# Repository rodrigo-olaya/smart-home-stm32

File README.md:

# smart-home-stm32
Smart Home on STM32F4 board.

## Build and flash
```
make clean && make
openocd -f board/stm32f4discovery.cfg -c "program firmware.elf verify reset exit"
```

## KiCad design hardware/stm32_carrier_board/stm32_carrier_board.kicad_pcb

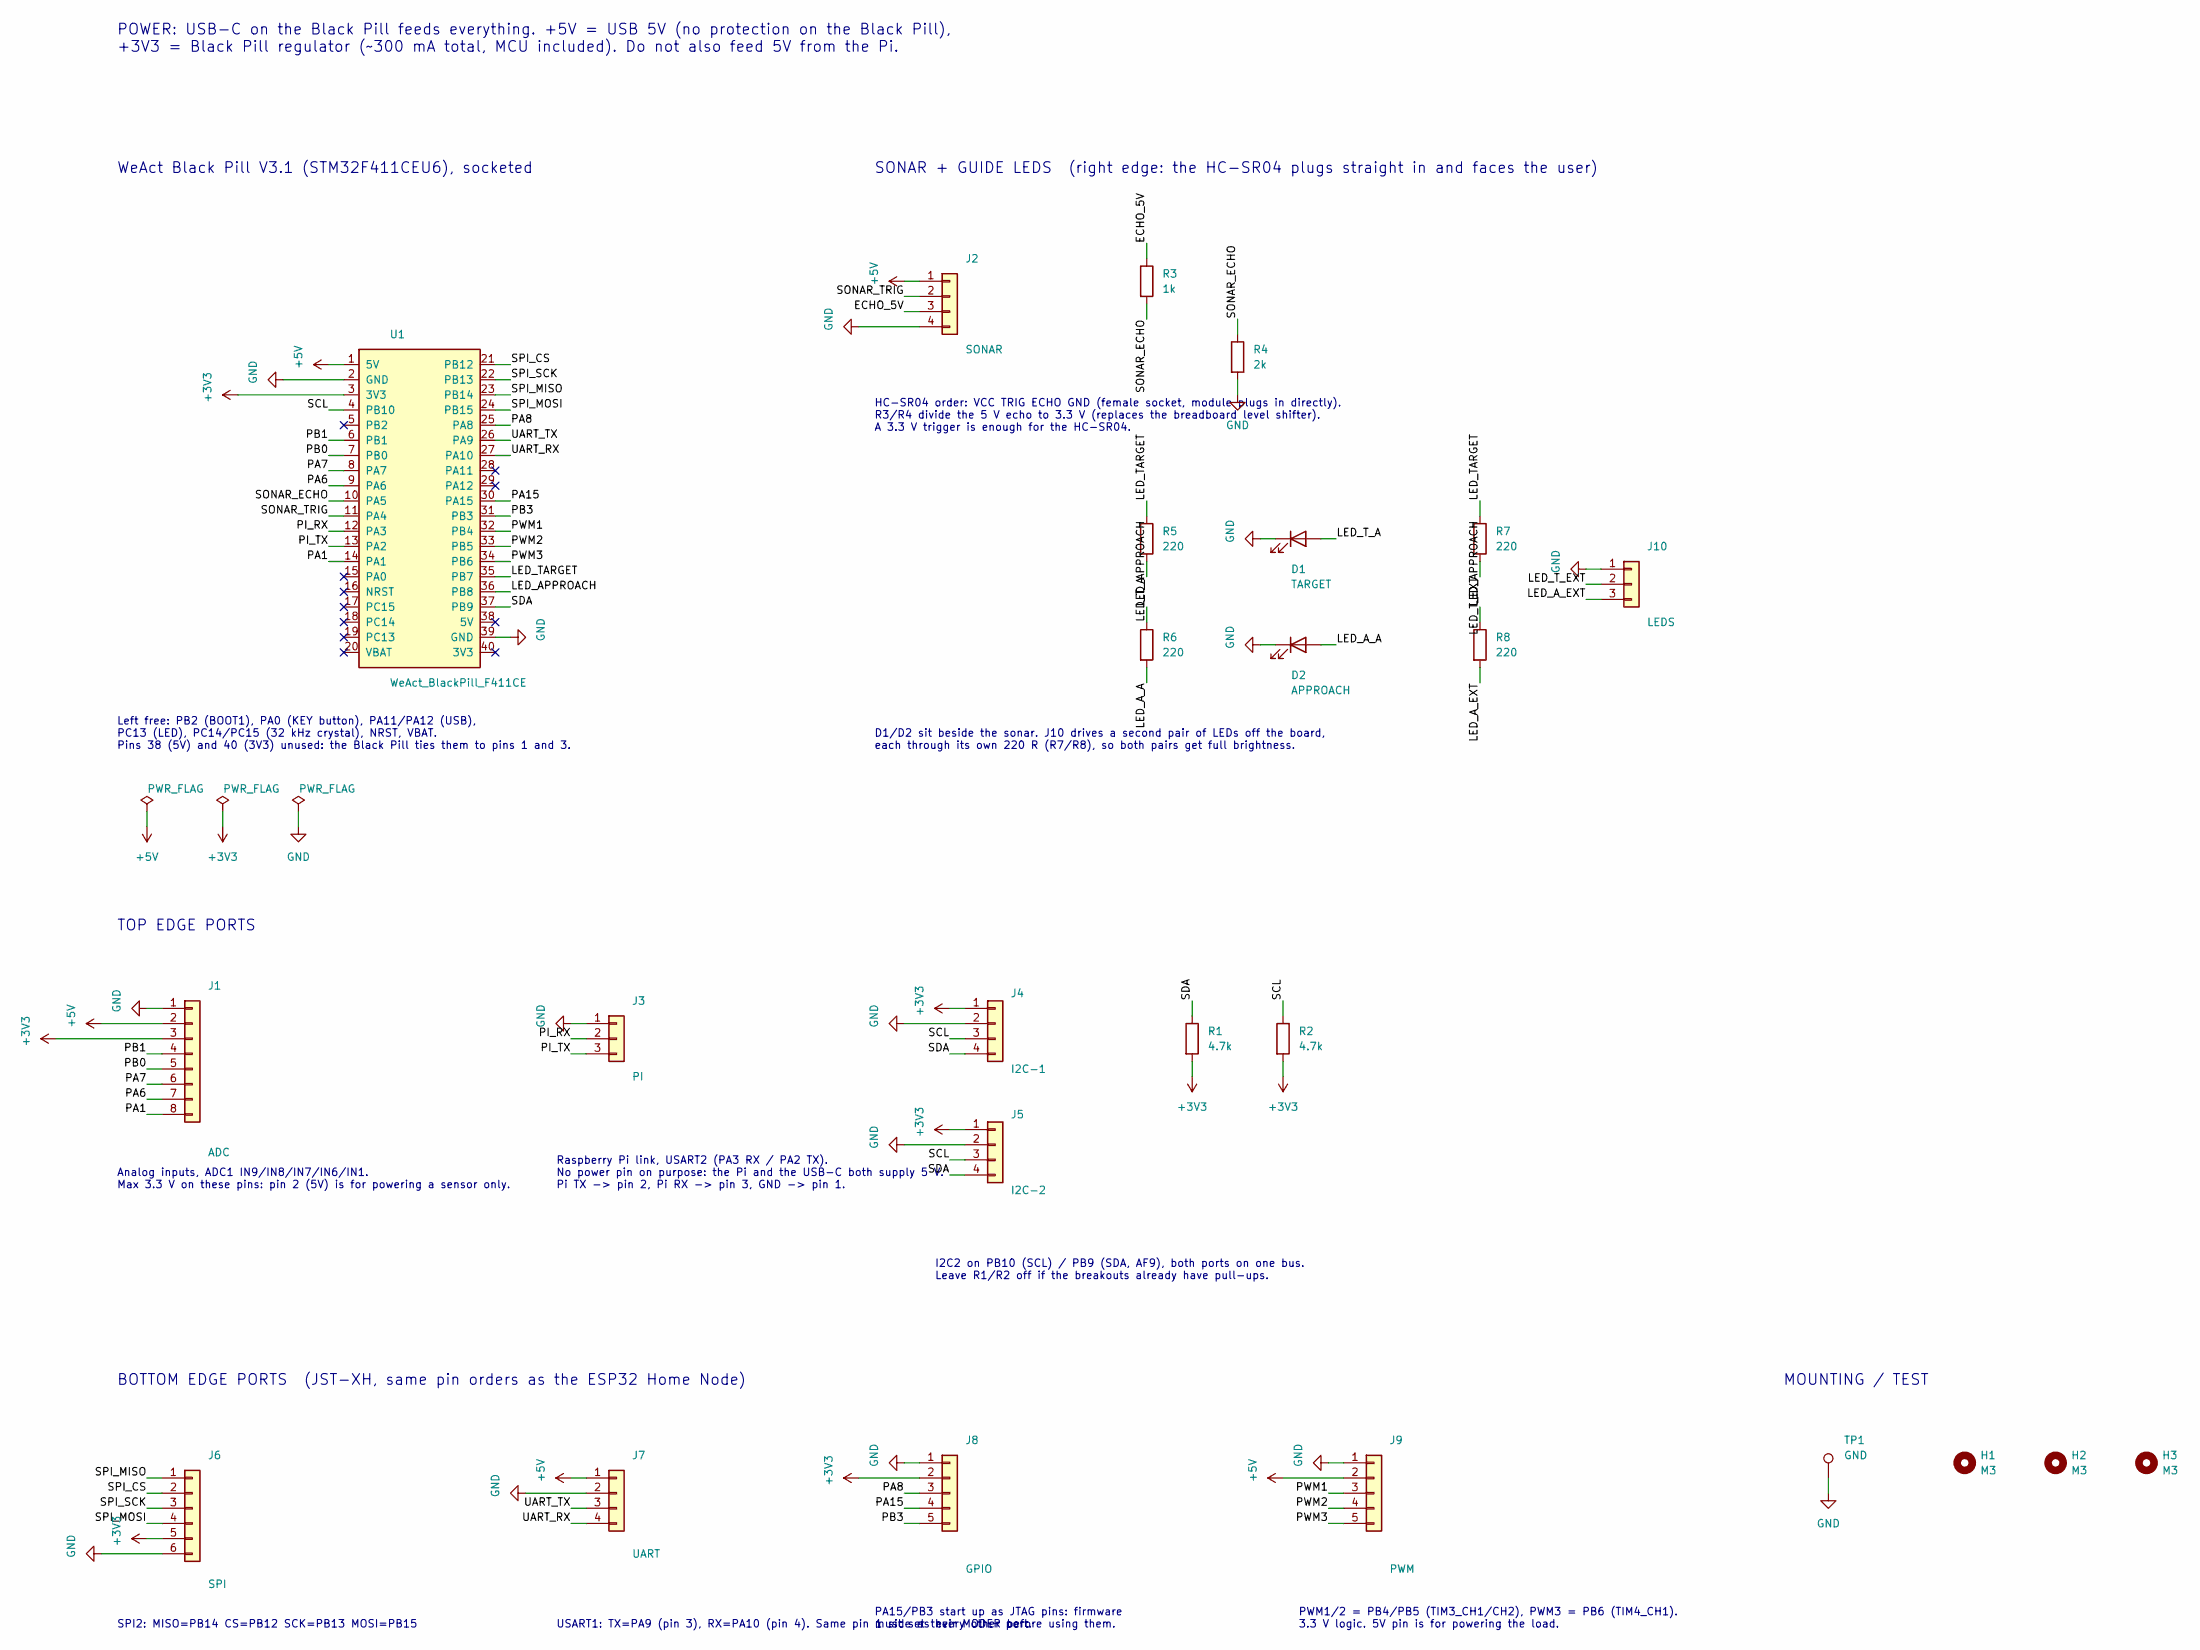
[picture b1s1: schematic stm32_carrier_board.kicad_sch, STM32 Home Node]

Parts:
D1: TARGET; LED_D5.0mm
D2: APPROACH; LED_D5.0mm
H1, H2, H3: M3; MountingHole_3.2mm_M3
J1: ADC; JST_XH_B8B-XH-A_1x08_P2.50mm_Vertical
J2: SONAR; PinSocket_1x04_P2.54mm_Vertical
J3: PI; JST_XH_B3B-XH-A_1x03_P2.50mm_Vertical
J4: I2C-1; JST_XH_B4B-XH-A_1x04_P2.50mm_Vertical
J5: I2C-2; JST_XH_B4B-XH-A_1x04_P2.50mm_Vertical
J6: SPI; JST_XH_B6B-XH-A_1x06_P2.50mm_Vertical
J7: UART; JST_XH_B4B-XH-A_1x04_P2.50mm_Vertical
J8: GPIO; JST_XH_B5B-XH-A_1x05_P2.50mm_Vertical
J9: PWM; JST_XH_B5B-XH-A_1x05_P2.50mm_Vertical
J10: LEDS; JST_XH_B3B-XH-A_1x03_P2.50mm_Vertical
R1, R2: 4.7k; R_Axial_DIN0207_L6.3mm_D2.5mm_P7.62mm_Horizontal
R3: 1k; R_Axial_DIN0207_L6.3mm_D2.5mm_P7.62mm_Horizontal
R4: 2k; R_Axial_DIN0207_L6.3mm_D2.5mm_P7.62mm_Horizontal
R5, R6, R7, R8: 220; R_Axial_DIN0207_L6.3mm_D2.5mm_P7.62mm_Horizontal
TP1: GND; TestPoint_THTPad_D2.0mm_Drill1.0mm
U1: WeAct_BlackPill_F411CE; WeAct_BlackPill_Socket

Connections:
+3V3: J1.3, J4.1, J5.1, J6.5, J8.2, R1.2, R2.2, U1.3 (3V3)
+5V: J1.2, J2.1, J7.1, J9.2, U1.1 (5V)
/ECHO_5V: J2.3, R3.1
/LED_APPROACH: R6.1, R8.1, U1.36 (PB8)
/LED_A_A: D2.2 (A), R6.2
/LED_A_EXT: J10.3, R8.2
/LED_TARGET: R5.1, R7.1, U1.35 (PB7)
/LED_T_A: D1.2 (A), R5.2
/LED_T_EXT: J10.2, R7.2
/PA1: J1.8, U1.14 (PA1)
/PA6: J1.7, U1.9 (PA6)
/PA7: J1.6, U1.8 (PA7)
/PA8: J8.3, U1.25 (PA8)
/PA15: J8.4, U1.30 (PA15)
/PB0: J1.5, U1.7 (PB0)
/PB1: J1.4, U1.6 (PB1)
/PB3: J8.5, U1.31 (PB3)
/PI_RX: J3.2, U1.12 (PA3)
/PI_TX: J3.3, U1.13 (PA2)
/PWM1: J9.3, U1.32 (PB4)
/PWM2: J9.4, U1.33 (PB5)
/PWM3: J9.5, U1.34 (PB6)
/SCL: J4.3, J5.3, R2.1, U1.4 (PB10)
/SDA: J4.4, J5.4, R1.1, U1.37 (PB9)
/SONAR_ECHO: R3.2, R4.1, U1.10 (PA5)
/SONAR_TRIG: J2.2, U1.11 (PA4)
/SPI_CS: J6.2, U1.21 (PB12)
/SPI_MISO: J6.1, U1.23 (PB14)
/SPI_MOSI: J6.4, U1.24 (PB15)
/SPI_SCK: J6.3, U1.22 (PB13)
/UART_RX: J7.4, U1.27 (PA10)
/UART_TX: J7.3, U1.26 (PA9)
GND: D1.1 (K), D2.1 (K), J1.1, J2.4, J3.1, J4.2, J5.2, J6.6, J7.2, J8.1, J9.1, J10.1, R4.2, TP1.1, U1.2 (GND), U1.39 (GND)

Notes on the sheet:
POWER: USB-C on the Black Pill feeds everything. +5V = USB 5V (no protection on the Black Pill), +3V3 = Black Pill regulator (~300 mA total, MCU included). Do not also feed 5V from the Pi.
WeAct Black Pill V3.1 (STM32F411CEU6), socketed
Left free: PB2 (BOOT1), PA0 (KEY button), PA11/PA12 (USB), PC13 (LED), PC14/PC15 (32 kHz crystal), NRST, VBAT. Pins 38 (5V) and 40 (3V3) unused: the Black Pill ties them to pins 1 and 3.
SONAR + GUIDE LEDS (right edge: the HC-SR04 plugs straight in and faces the user)
HC-SR04 order: VCC TRIG ECHO GND (female socket, module plugs in directly). R3/R4 divide the 5 V echo to 3.3 V (replaces the breadboard level shifter). A 3.3 V trigger is enough for the HC-SR04.
D1/D2 sit beside the sonar. J10 drives a second pair of LEDs off the board, each through its own 220 R (R7/R8), so both pairs get full brightness.
TOP EDGE PORTS
Analog inputs, ADC1 IN9/IN8/IN7/IN6/IN1. Max 3.3 V on these pins: pin 2 (5V) is for powering a sensor only.
Raspberry Pi link, USART2 (PA3 RX / PA2 TX). No power pin on purpose: the Pi and the USB-C both supply 5 V. Pi TX -> pin 2, Pi RX -> pin 3, GND -> pin 1.
I2C2 on PB10 (SCL) / PB9 (SDA, AF9), both ports on one bus. Leave R1/R2 off if the breakouts already have pull-ups.
BOTTOM EDGE PORTS (JST-XH, same pin orders as the ESP32 Home Node)
SPI2: MISO=PB14 CS=PB12 SCK=PB13 MOSI=PB15
USART1: TX=PA9 (pin 3), RX=PA10 (pin 4). Same pin 1 side as every other port.
PA15/PB3 start up as JTAG pins: firmware must set their MODER before using them.
PWM1/2 = PB4/PB5 (TIM3_CH1/CH2), PWM3 = PB6 (TIM4_CH1). 3.3 V logic. 5V pin is for powering the load.
MOUNTING / TEST

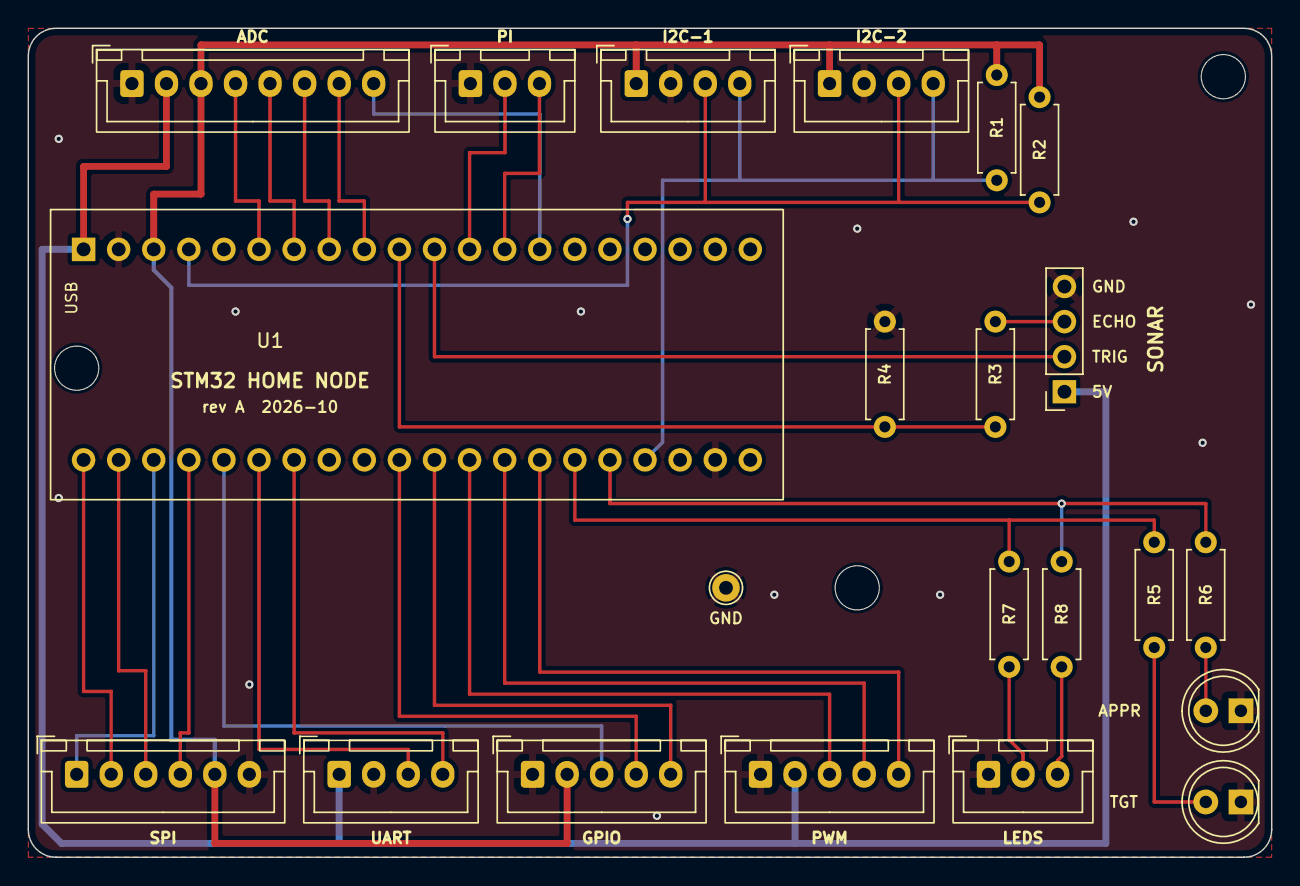
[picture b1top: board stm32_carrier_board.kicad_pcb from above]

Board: 2 copper layers, 90.0 x 60.0 mm, 25 parts (0 on the bottom side), 33 nets.

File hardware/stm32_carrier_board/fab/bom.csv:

"Reference","Value","Footprint","QUANTITY"
"D1","TARGET","LED_THT:LED_D5.0mm","1"
"D2","APPROACH","LED_THT:LED_D5.0mm","1"
"J1","ADC","Connector_JST:JST_XH_B8B-XH-A_1x08_P2.50mm_Vertical","1"
"J2","SONAR","Connector_PinSocket_2.54mm:PinSocket_1x04_P2.54mm_Vertical","1"
"J3","PI","Connector_JST:JST_XH_B3B-XH-A_1x03_P2.50mm_Vertical","1"
"J4","I2C-1","Connector_JST:JST_XH_B4B-XH-A_1x04_P2.50mm_Vertical","1"
"J5","I2C-2","Connector_JST:JST_XH_B4B-XH-A_1x04_P2.50mm_Vertical","1"
"J6","SPI","Connector_JST:JST_XH_B6B-XH-A_1x06_P2.50mm_Vertical","1"
"J7","UART","Connector_JST:JST_XH_B4B-XH-A_1x04_P2.50mm_Vertical","1"
"J8","GPIO","Connector_JST:JST_XH_B5B-XH-A_1x05_P2.50mm_Vertical","1"
"J9","PWM","Connector_JST:JST_XH_B5B-XH-A_1x05_P2.50mm_Vertical","1"
"J10","LEDS","Connector_JST:JST_XH_B3B-XH-A_1x03_P2.50mm_Vertical","1"
"R1,R2","4.7k","Resistor_THT:R_Axial_DIN0207_L6.3mm_D2.5mm_P7.62mm_Horizontal","2"
"R3","1k","Resistor_THT:R_Axial_DIN0207_L6.3mm_D2.5mm_P7.62mm_Horizontal","1"
"R4","2k","Resistor_THT:R_Axial_DIN0207_L6.3mm_D2.5mm_P7.62mm_Horizontal","1"
"R5-R8","220","Resistor_THT:R_Axial_DIN0207_L6.3mm_D2.5mm_P7.62mm_Horizontal","4"
"U1","WeAct_BlackPill_F411CE","stm32_board_fp:WeAct_BlackPill_Socket","1"

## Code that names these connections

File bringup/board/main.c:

#include <stdint.h>

// Carrier board test, polling only (no interrupts).
//   PA4 = TRIG (out)   PA5 = ECHO (in, divided to 3.3 V by R3/R4)
//   PB7 = D1 target LED   PB8 = D2 approach LED   (pin HIGH = LED on)
//   PC13 = Black Pill LED (pin LOW = LED on)
//
// On boot: D1, then D2, then PC13 each light for 0.4 s (checks the LEDs).
// Then it loops on the sonar:
//   closer than 30 cm   -> D1 (target) on
//   30 to 80 cm         -> D2 (approach) on
//   farther / no echo   -> both off
//   PC13 is on whenever an echo was received.
// TIM2 free-runs at 1 MHz (HSI 16 MHz / 16), so one count = 1 us.

#define RCC_AHB1ENR   (*(volatile uint32_t *)0x40023830)
#define RCC_APB1ENR   (*(volatile uint32_t *)0x40023840)

#define GPIOA_MODER   (*(volatile uint32_t *)0x40020000)
#define GPIOA_IDR     (*(volatile uint32_t *)0x40020010)
#define GPIOA_BSRR    (*(volatile uint32_t *)0x40020018)
#define GPIOB_MODER   (*(volatile uint32_t *)0x40020400)
#define GPIOB_BSRR    (*(volatile uint32_t *)0x40020418)
#define GPIOC_MODER   (*(volatile uint32_t *)0x40020800)
#define GPIOC_BSRR    (*(volatile uint32_t *)0x40020818)

#define TIM2_CR1      (*(volatile uint32_t *)0x40000000)
#define TIM2_EGR      (*(volatile uint32_t *)0x40000014)
#define TIM2_CNT      (*(volatile uint32_t *)0x40000024)
#define TIM2_PSC      (*(volatile uint32_t *)0x40000028)
#define TIM2_ARR      (*(volatile uint32_t *)0x4000002C)

#define TRIG_PIN      4
#define ECHO_PIN      5
#define TARGET_PIN    7     // PB7, D1
#define APPROACH_PIN  8     // PB8, D2
#define BOARD_LED_PIN 13    // PC13
#define TARGET_CM     30
#define APPROACH_CM   80
#define ECHO_TIMEOUT_US 30000u

static void mode_output(volatile uint32_t *moder, int pin) {
    *moder &= ~(3u << (pin * 2));
    *moder |=  (1u << (pin * 2));
}

static void d1(int on)    { GPIOB_BSRR = on ? (1u << TARGET_PIN)   : (1u << (TARGET_PIN + 16)); }
static void d2(int on)    { GPIOB_BSRR = on ? (1u << APPROACH_PIN) : (1u << (APPROACH_PIN + 16)); }
static void board(int on) { GPIOC_BSRR = on ? (1u << (BOARD_LED_PIN + 16)) : (1u << BOARD_LED_PIN); }

static void delay_us(uint32_t us) {
    uint32_t start = TIM2_CNT;
    while ((TIM2_CNT - start) < us) { }
}

// Echo pulse width in us, or 0 if no echo came back in time.
static uint32_t measure_us(void) {
    GPIOA_BSRR = (1u << TRIG_PIN);              // 10 us TRIG pulse
    delay_us(10);
    GPIOA_BSRR = (1u << (TRIG_PIN + 16));

    uint32_t t0 = TIM2_CNT;
    while (!(GPIOA_IDR & (1u << ECHO_PIN))) {
        if ((TIM2_CNT - t0) > ECHO_TIMEOUT_US) return 0;
    }
    uint32_t rise = TIM2_CNT;
    while (GPIOA_IDR & (1u << ECHO_PIN)) {
        if ((TIM2_CNT - rise) > ECHO_TIMEOUT_US) return 0;
    }
    return TIM2_CNT - rise;
}

int main(void) {
    RCC_AHB1ENR |= (1u << 0) | (1u << 1) | (1u << 2);   // GPIOA, GPIOB, GPIOC
    RCC_APB1ENR |= (1u << 0);                           // TIM2

    mode_output(&GPIOA_MODER, TRIG_PIN);                // ECHO stays input
    mode_output(&GPIOB_MODER, TARGET_PIN);
    mode_output(&GPIOB_MODER, APPROACH_PIN);
    mode_output(&GPIOC_MODER, BOARD_LED_PIN);
    d1(0); d2(0); board(0);

    TIM2_PSC = 15;                                      // 16 MHz / 16 = 1 MHz
    TIM2_ARR = 0xFFFFFFFFu;                             // 32-bit on the F4
    TIM2_EGR = 1;                                       // load PSC now
    TIM2_CR1 = 1;                                       // start counting

    // LED self-test
    d1(1);    delay_us(400000); d1(0);
    d2(1);    delay_us(400000); d2(0);
    board(1); delay_us(400000); board(0);

    while (1) {
        uint32_t us = measure_us();
        uint32_t cm = us / 58;                          // ~58 us per cm round trip
        board(us != 0);
        d1(us != 0 && cm < TARGET_CM);
        d2(us != 0 && cm >= TARGET_CM && cm < APPROACH_CM);
        delay_us(60000);                                // >60 ms between pings
    }
}

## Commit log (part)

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2026-06-19 linker
2026-06-19 blinky
2026-06-19 uart registers
2026-06-19 UART init
2026-06-20 Remove magic numbers
2026-06-20 uart write byte
2026-06-21 UART working on logic analyzer
2026-06-24 UART working on logic analyzer and pi
2026-06-27 Move GPIO and RCC to their own registers file
2026-06-27 start intitializing timers
2026-06-27 finish C implementation of timers
2026-06-27 Tim2 ISR complete, working on LA and PI
2026-06-28 uart dequeue
2026-06-28 UART ISR
